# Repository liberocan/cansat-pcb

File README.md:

# cansat-circuits
Diagrams, circuits, schemas and gerber files of LiberoCAN free and open source CanSat

## Components
Check out our [docs](https://github.com/liberocan/cansat-docs/blob/main/CIRCUIT.md) for components.

## Pictures
### PCB

## TO-DO
- [X] Creation of part list
- [X] Ordering of parts
- [] Connecting and testing parts
- [x] Creation of schematics
- [x] Creation of PCB
- [x] Creation of gerber files for manufacturing
- [] Ordering and testing

## License
This free and open source hardware project is licensed with [CERN Open Hardware License Version 2 - Weakly Reciprocal](https://ohwr.org/project/cernohl/-/wikis/uploads/82b567f43ce515395f7ddbfbad7a8806/cern_ohl_w_v2.txt). The schematics are licensed with [Creative Commons Attribution-ShareAlike 4.0](https://creativecommons.org/licenses/by-sa/4.0/deed.en). The project has been certified by OSHW as Open Source Hardware (UID: [IT000016](https://certification.oshwa.org/it000016.html)).
</br>

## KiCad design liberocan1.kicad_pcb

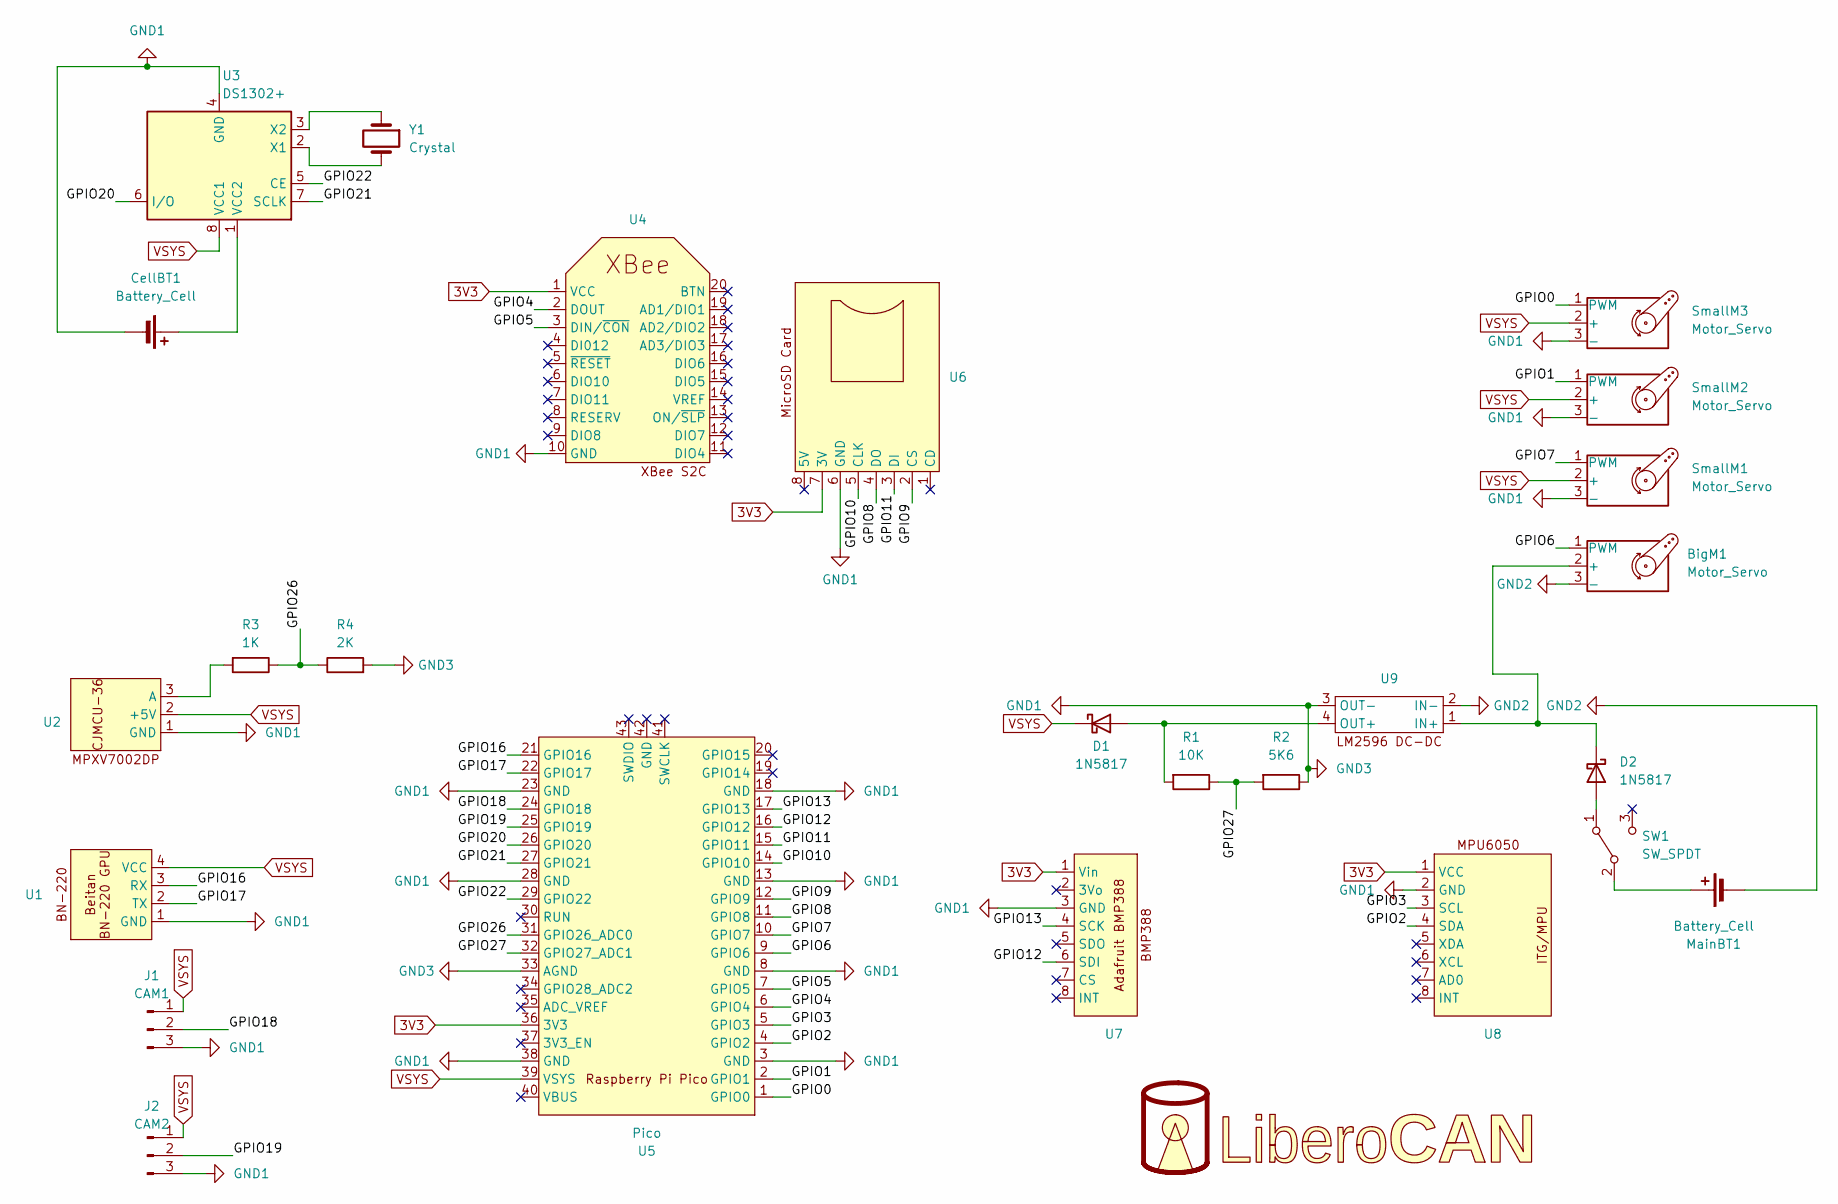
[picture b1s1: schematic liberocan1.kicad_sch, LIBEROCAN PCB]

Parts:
BigM1: Motor_Servo; PinHeader_1x03_P2.54mm_Vertical
CellBT1: Battery_Cell; BatteryHolder_Keystone_103_1x20mm
D1, D2: 1N5817; D_DO-41_SOD81_P7.62mm_Horizontal
J1: CAM1; PinHeader_1x03_P2.54mm_Vertical
J2: CAM2; PinHeader_1x03_P2.54mm_Vertical
MainBT1: Battery_Cell; PinHeader_1x02_P2.54mm_Vertical
R1: 10K; R_Axial_DIN0204_L3.6mm_D1.6mm_P5.08mm_Horizontal
R2: 5K6; R_Axial_DIN0204_L3.6mm_D1.6mm_P5.08mm_Horizontal
R3: 1K; R_Axial_DIN0204_L3.6mm_D1.6mm_P5.08mm_Horizontal
R4: 2K; R_Axial_DIN0204_L3.6mm_D1.6mm_P5.08mm_Horizontal
SW1: SW_SPDT; SW_E-Switch_EG1271_SPDT
SmallM1, SmallM2, SmallM3: Motor_Servo; PinHeader_1x03_P2.54mm_Vertical
U1: BN-220
U2: PinHeader_1x03_P2.54mm_Vertical
U3: DS1302+; DIP-8_W7.62mm
U4: XBee S2C
U5: Pico; RPi_Pico_SMD_TH
U6: Adafruit MicroSD Breakout
U7: Adafruit BMP388 Blue
U8: MPU6050 Module
U9: LM2596 Voltage Regulator board
U10: (no value)
Y1: Crystal; Crystal_C38-LF_D3.0mm_L8.0mm_Vertical

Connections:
3V3: U4.1 (VCC), U5.36 (3V3), U6.7 (3V), U7.1 (Vin), U8.1 (VCC)
/GPIO0: SmallM3.1 (PWM), U5.1 (GPIO0)
/GPIO1: SmallM2.1 (PWM), U5.2 (GPIO1)
/GPIO2: U5.4 (GPIO2), U8.4 (SDA)
/GPIO3: U5.5 (GPIO3), U8.3 (SCL)
/GPIO4: U4.2 (DOUT), U5.6 (GPIO4)
/GPIO5: U4.3 (DIN/~CON), U5.7 (GPIO5)
/GPIO6: BigM1.1 (PWM), U5.9 (GPIO6)
/GPIO7: SmallM1.1 (PWM), U5.10 (GPIO7)
/GPIO8: U5.11 (GPIO8), U6.4 (DO)
/GPIO9: U5.12 (GPIO9), U6.2 (CS)
/GPIO10: U5.14 (GPIO10), U6.5 (CLK)
/GPIO11: U5.15 (GPIO11), U6.3 (DI)
/GPIO12: U5.16 (GPIO12), U7.6 (SDI)
/GPIO13: U5.17 (GPIO13), U7.4 (SCK)
/GPIO16: U1.3 (RX), U5.21 (GPIO16)
/GPIO17: U1.2 (TX), U5.22 (GPIO17)
/GPIO18: J1.2, U5.24 (GPIO18)
/GPIO19: J2.2, U5.25 (GPIO19)
/GPIO20: U3.6 (I/O), U5.26 (GPIO20)
/GPIO21: U3.7 (SCLK), U5.27 (GPIO21)
/GPIO22: U3.5 (CE), U5.29 (GPIO22)
/GPIO26: R3.1, R4.1, U5.31 (GPIO26_ADC0)
/GPIO27: R1.1, R2.2, U5.32 (GPIO27_ADC1)
GND1: CellBT1.2 (-), J1.3, J2.3, R2.1, R4.2, SmallM1.3 (-), SmallM2.3 (-), SmallM3.3 (-), U1.1 (GND), U2.1 (GND), U3.4 (GND), U4.10 (GND), U5.3 (GND), U5.8 (GND), U5.13 (GND), U5.18 (GND), U5.23 (GND), U5.28 (GND), U5.33 (AGND), U5.38 (GND), U6.6 (GND), U7.3 (GND), U8.2 (GND), U9.3 (OUT-)
GND2: BigM1.3 (-), MainBT1.2 (-), U9.2 (IN-)
unnamed: BigM1.2 (+), D2.1 (K), U9.1 (IN+)
unnamed: CellBT1.1 (+), U3.1 (VCC2)
unnamed: D1.2 (A), R1.2, U9.4 (OUT+)
unnamed: D2.2 (A), SW1.1 (A)
unnamed: MainBT1.1 (+), SW1.2 (B)
unnamed: R3.2, U2.3 (A)
unnamed: U3.2 (X1), Y1.2
unnamed: U3.3 (X2), Y1.1
VSYS: D1.1 (K), J1.1, J2.1, SmallM1.2 (+), SmallM2.2 (+), SmallM3.2 (+), U1.4 (VCC), U2.2 (+5V), U3.8 (VCC1), U5.39 (VSYS)

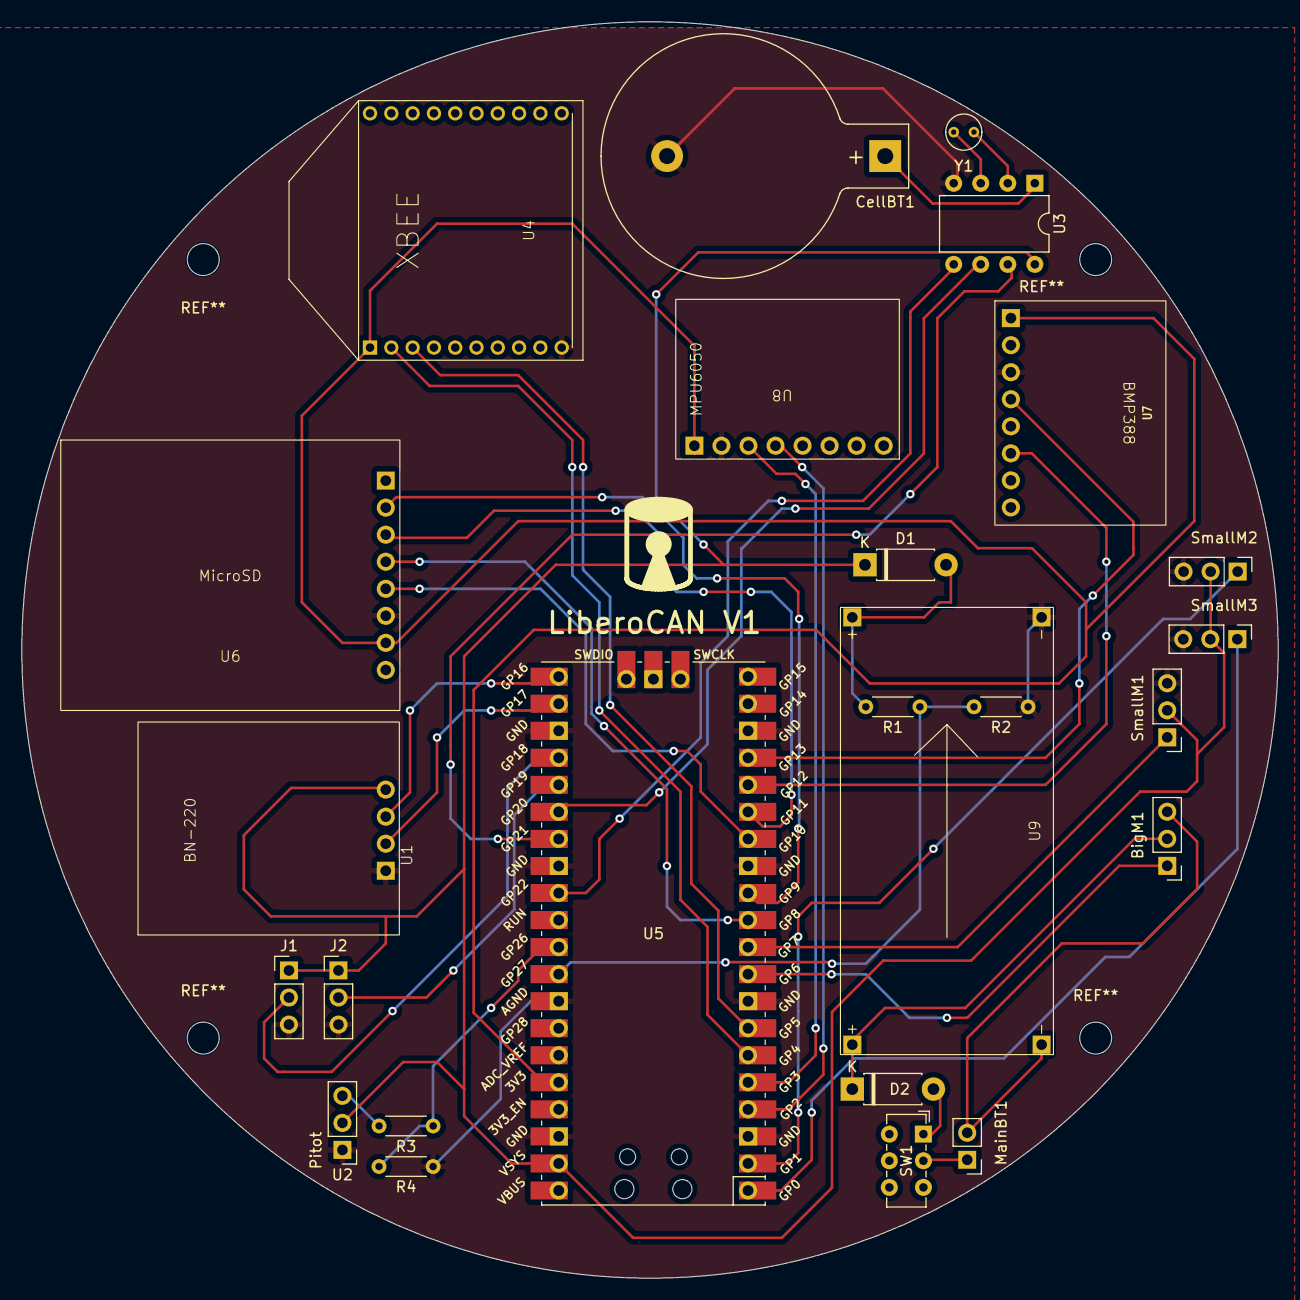
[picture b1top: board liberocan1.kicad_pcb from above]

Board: 2 copper layers, 118.0 x 118.0 mm, 25 parts (0 on the bottom side), 35 nets.

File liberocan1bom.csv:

"Id";"Designator";"Footprint";"Quantity";"Designation";"Supplier and ref";
1;"J2";"PinHeader_1x03_P2.54mm_Vertical";1;"CAM2";;;
2;"U2";"PinHeader_1x03_P2.54mm_Vertical";1;"~";;;
3;"U6";"Adafruit MicroSD Breakout";1;"~";;;
4;"U1";"BN-220";1;"~";;;
5;"R3";"R_Axial_DIN0204_L3.6mm_D1.6mm_P5.08mm_Horizontal";1;"1K";;;
6;"MainBT1";"PinHeader_1x02_P2.54mm_Vertical";1;"Battery_Cell";;;
7;"D2,D1";"D_DO-41_SOD81_P7.62mm_Horizontal";2;"1N5817";;;
8;"SmallM3,BigM1,SmallM2,SmallM1";"PinHeader_1x03_P2.54mm_Vertical";4;"Motor_Servo";;;
9;"U9";"LM2596 Voltage Regulator board";1;"~";;;
10;"J1";"PinHeader_1x03_P2.54mm_Vertical";1;"CAM1";;;
11;"U5";"RPi_Pico_SMD_TH";1;"Pico";;;
12;"CellBT1";"BatteryHolder_Keystone_103_1x20mm";1;"Battery_Cell";;;
13;"U3";"DIP-8_W7.62mm";1;"DS1302+";;;
14;"U4";"XBee S2C";1;"~";;;
15;"Y1";"Crystal_C38-LF_D3.0mm_L8.0mm_Vertical";1;"Crystal";;;
16;"R2";"R_Axial_DIN0204_L3.6mm_D1.6mm_P5.08mm_Horizontal";1;"5K6";;;
17;"R4";"R_Axial_DIN0204_L3.6mm_D1.6mm_P5.08mm_Horizontal";1;"2K";;;
18;"SW1";"SW_E-Switch_EG1271_SPDT";1;"SW_SPDT";;;
19;"U7";"Adafruit BMP388 Blue";1;"~";;;
20;"R1";"R_Axial_DIN0204_L3.6mm_D1.6mm_P5.08mm_Horizontal";1;"10K";;;
21;"U8";"MPU6050 Module";1;"~";;;

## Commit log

2023-11-09 add files and directories
2023-11-09 edit README
2023-11-18 first version of schematic
2023-11-18 export last minor revision
2023-11-18 save and export minor revision
2023-11-18 fix minor issue
2023-11-21 add new schematic and some custom footprints
2023-11-22 edit schematic, complete all footprints and annotate them with the symbols
2023-11-23 add pcb and 3d files
2023-11-23 save changes
2023-11-23 edit pcb and generate gerber files
2023-11-23 solve issues and edit readme
2023-11-24 reduce pcb size
2023-11-24 move vector files
2023-12-15 Update PCB
2024-09-20 rebrand
2024-09-20 add license
2024-09-20 Update LICENSE
2024-10-03 add OSHW cert
2024-10-03 add OSHW on pcb
2024-10-03 add oshw cert image
2024-10-03 add br
2024-10-03 add link

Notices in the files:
liberocan1.kicad_pcb:
License: CC BY-SA 4.0
